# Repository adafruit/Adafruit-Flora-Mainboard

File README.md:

# Adafruit Flora Mainboard PCB Files
<a href="http://www.adafruit.com/products/659"><br/>
Click here to purchase one from the Adafruit shop</a>

FLORA is Adafruit's fully-featured wearable electronics platform. It's a round, sewable, Arduino-compatible microcontroller designed to empower amazing wearables projects.FLORA comes with Adafruit's support, tutorials and projects. Check out dozens of FLORA tutorials on the Adafruit Learning System, with more added all the time!

The FLORA is small (1.75" diameter, weighing 4.4 grams). The FLORA family also has the best stainless steel threads, sensors, GPS modules and chainable LED NeoPixels, perfect accessories for the FLORA main board. 

The FLORA has built-in USB support. Built in USB means you plug it in to program it, it just shows up - all you need is a Micro-B USB cable, no additional purchases are needed! We have a modified version of the Arduino IDE so Mac & Windows users can get started fast - or with the new 1.6.4+ Arduino IDE, it takes only a few seconds to add Flora-support. The FLORA has USB HID support, so it can act like a mouse or keyboard to attach directly to computers.

This is the PCB for the Adafruit Flora Mainboard. The format is EagleCAD schematic and board layout
- http://adafruit.com/products/659

### License

Adafruit invests time and resources providing this open source design, please support Adafruit and open-source hardware by purchasing products from [Adafruit](https://www.adafruit.com)!

All text above must be included in any redistribution

Designed by Limor Fried/Ladyada for Adafruit Industries.
Creative Commons Attribution/Share-Alike, all text above must be included in any redistribution. 
See license.txt for additional information.

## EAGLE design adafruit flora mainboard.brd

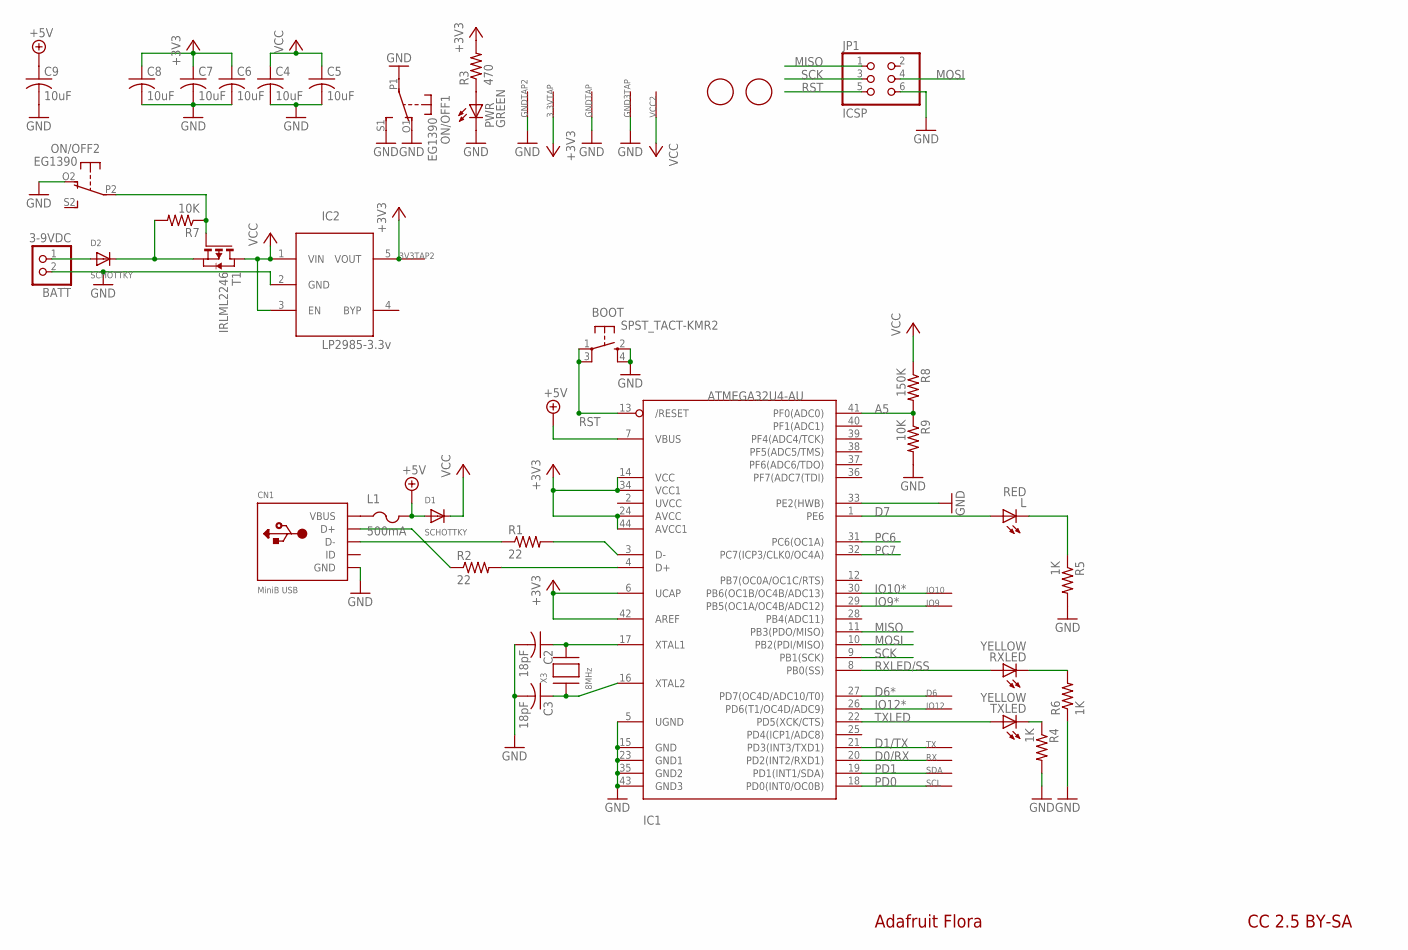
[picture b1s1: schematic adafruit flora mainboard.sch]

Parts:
3.3VTAP, 3V3TAP2: SEWTAP-2.0IN; SEWINGTAP_2.0
BATT: 3-9VDC; JST-PH-2-SMT-RA
BOOT: SPST_TACT-KMR2; KMR2
C2, C3: 18pF; C0805K
C4, C5, C6, C7, C8, C9: 10uF; C0805K
CN1: MiniB USB; USB-MINIB_LARGER
D1, D2: SCHOTTKY; SOD-123
D6: SEWTAP-2.0IN; SEWINGTAP_2.0
GND3TAP: SEWTAP-2.0IN; SEWINGTAP_2.0
GNDTAP, GNDTAP2: SEWTAP-2.0IN; SEWINGTAP_2.0
IC1: ATMEGA32U4-AU; TQFP44
IC2: LP2985-3.3v; SOT23-5L
IO9, IO10, IO12: SEWTAP-2.0IN; SEWINGTAP_2.0
JP1: ICSP; 2X03
L: RED; CHIPLED_0805
L1: 500mA; R1206
ON/OFF: EG1390
PWR: GREEN; CHIPLED_0805
R1, R2: 22; R0805
R3: 470; R0805
R4, R5, R6: 1K; R0805
R7, R9: 10K; R0805
R8: 150K; R0805
RX: SEWTAP-2.0IN; SEWINGTAP_2.0
RXLED: YELLOW; CHIPLED_0805
SCL: SEWTAP-2.0IN; SEWINGTAP_2.0
SDA: SEWTAP-2.0IN; SEWINGTAP_2.0
T1: IRLML2246; SOT-23
TX: SEWTAP-2.0IN; SEWINGTAP_2.0
TXLED: YELLOW; CHIPLED_0805
U$2, U$6: FIDUCIAL; FIDUCIAL_1MM
VCC2: SEWTAP-2.0IN; SEWINGTAP_2.0
X3: 8MHz; NX5032

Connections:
+3V3: 3.3VTAP.P$1, 3V3TAP2.P$1, C6.1, C7.1, C8.1, IC1.6 (UCAP), IC1.14 (VCC), IC1.24 (AVCC), IC1.34 (VCC1), IC1.42 (AREF), IC1.44 (AVCC1), IC2.5 (VOUT), R3.2
+5V: C9.1, D1.A, IC1.7 (VBUS), L1.2
A5: IC1.41 (PF0(ADC0)), R8.2, R9.1
D0/RX: IC1.20 (PD2(INT2/RXD1)), RX.P$1
D1/TX: IC1.21 (PD3(INT3/TXD1)), TX.P$1
D6*: D6.P$1, IC1.27 (PD7(OC4D/ADC10/T0))
D7: IC1.1 (PE6), L.A
GND: BATT.2 (1), BOOT.2 (S), BOOT.4 (S1), C2.2, C3.2, C4.2, C5.2, C6.2, C7.2, C8.2, C9.2, CN1.GND, GND3TAP.P$1, GNDTAP.P$1, GNDTAP2.P$1, IC1.5 (UGND), IC1.15 (GND), IC1.23 (GND1), IC1.33 (PE2(HWB)), IC1.35 (GND2), IC1.43 (GND3), IC2.2 (GND), JP1.6, ON/OFF.O1 (O), ON/OFF.O2 (O), ON/OFF.P1, ON/OFF.S1 (S), PWR.C, R4.2, R5.2, R6.1, R9.2
IO9*: IC1.29 (PB5(OC1A/OC4B/ADC12)), IO9.P$1
IO10*: IC1.30 (PB6(OC1B/OC4B/ADC13)), IO10.P$1
IO12*: IC1.26 (PD6(T1/OC4D/ADC9)), IO12.P$1
MISO: IC1.11 (PB3(PDO/MISO)), JP1.1
MOSI: IC1.10 (PB2(PDI/MISO)), JP1.4
unnamed: PWR.A, R3.1
unnamed: CN1.D+, R2.1
unnamed: IC1.3 (D-), R1.2
unnamed: IC1.4 (D+), R2.2
unnamed: CN1.D-, R1.1
unnamed: D2.C, R7.2, T1.2 (S)
unnamed: BATT.1 (2), D2.A
unnamed: C2.1, IC1.17 (XTAL1), X3.P$2
unnamed: C3.1, IC1.16 (XTAL2), X3.P$1
unnamed: L.C, R5.1
unnamed: R4.1, TXLED.C
unnamed: R6.2, RXLED.C
unnamed: ON/OFF.P2, R7.1, T1.3 (G)
PC6: IC1.31 (PC6(OC1A))
PC7: IC1.32 (PC7(ICP3/CLK0/OC4A))
PD0: IC1.18 (PD0(INT0/OC0B)), SCL.P$1
PD1: IC1.19 (PD1(INT1/SDA)), SDA.P$1
RST: BOOT.1, BOOT.3 (P1), IC1.13 (/RESET), JP1.5
RXLED/SS: IC1.8 (PB0(SS)), RXLED.A
SCK: IC1.9 (PB1(SCK)), JP1.3
TXLED: IC1.22 (PD5(XCK/CTS)), TXLED.A
VBUS: CN1.VBUS, L1.1
VCC: C4.1, C5.1, D1.C, IC2.1 (VIN), IC2.3 (EN), R8.1, T1.1 (D), VCC2.P$1

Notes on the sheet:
Adafruit Flora
CC 2.5 BY-SA

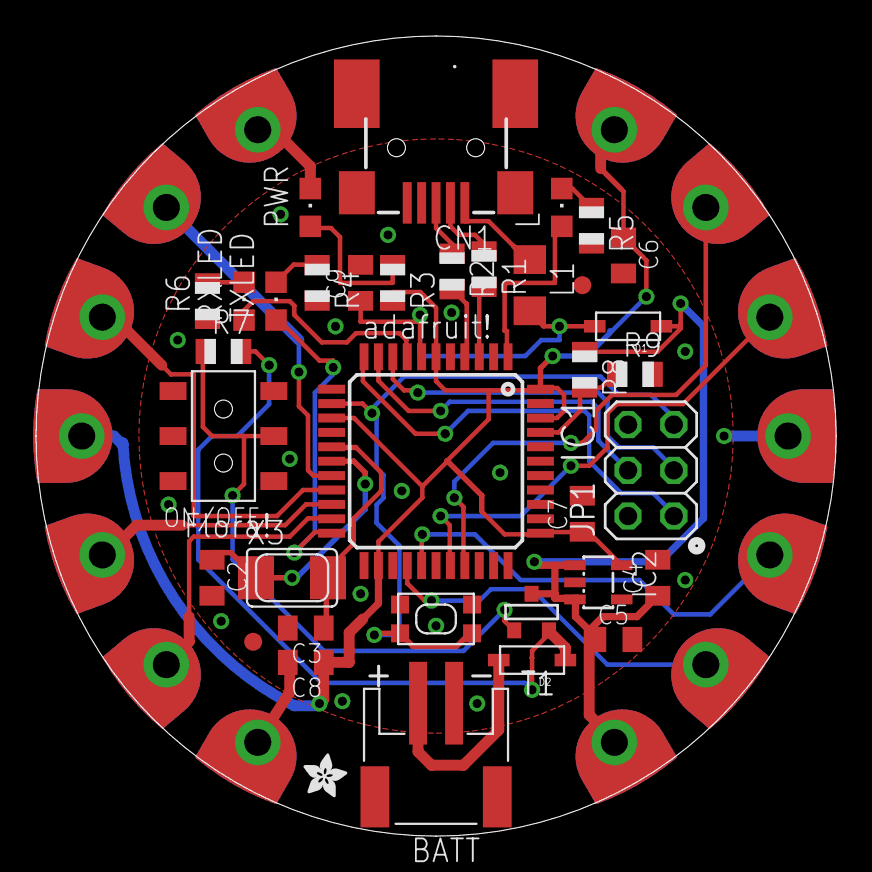
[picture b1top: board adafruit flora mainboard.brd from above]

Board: 2 copper layers, 44.5 x 44.5 mm, 51 parts (1 on the bottom side), 34 nets.

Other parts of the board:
U$3: ADAFRUIT_2.5MM
U$4: FLORAMED

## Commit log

2013-01-14 commit!
2013-01-14 read!
2013-08-16 pdf printouts of the two schemas

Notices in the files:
parts and their libraries:
microbuilder: This work is placed in the public domain, and may be freely used for commercial and non-commercial work with the following conditions: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
